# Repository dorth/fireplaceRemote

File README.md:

fireplaceRemote
===============

Arduino project for a remote control to a gas fireplace

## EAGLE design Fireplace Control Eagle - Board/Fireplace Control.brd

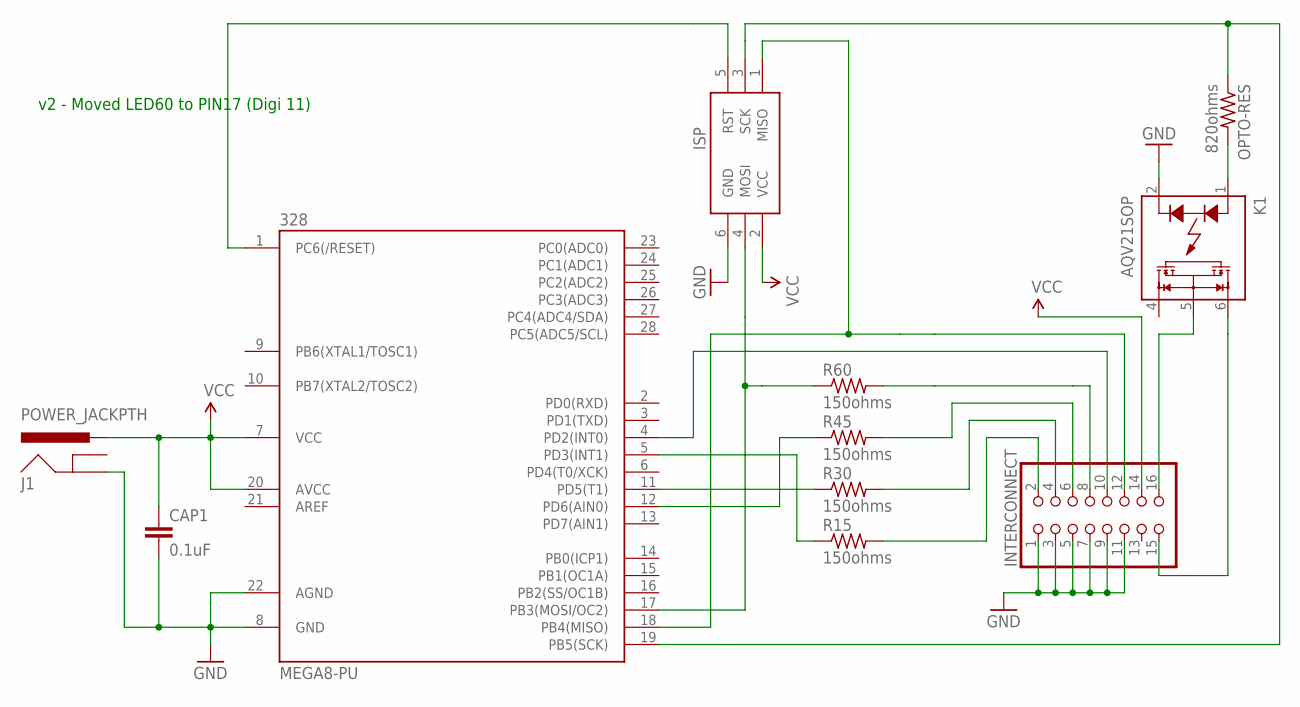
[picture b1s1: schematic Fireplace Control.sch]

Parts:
328: MEGA8-PU; DIL28-3
CAP1: 0.1uF; CAP-PTH-SMALL-KIT
INTERCONNECT: PINHD-2X8; 2X08
ISP: AVRISP-6; AVRISP
J1: POWER_JACKPTH; POWER_JACK_PTH
K1: AQV21SOP; SOP06
OPTO-RES: 820ohms; 0207/2V
R15, R30, R45, R60: 150ohms; 0207/2V

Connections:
15+: INTERCONNECT.2, R15.2
30+: INTERCONNECT.4, R30.2
45+: INTERCONNECT.6, R45.2
60+: INTERCONNECT.8, R60.2
GND: 328.8 (GND), 328.22 (AGND), CAP1.2, INTERCONNECT.1, INTERCONNECT.3, INTERCONNECT.5, INTERCONNECT.7, INTERCONNECT.9, INTERCONNECT.11, ISP.6 (GND), J1.GND, K1.2 (K)
unnamed: 328.11 (PD5(T1)), R30.1
unnamed: INTERCONNECT.15, K1.6 (D1)
unnamed: 328.12 (PD6(AIN0)), R45.1
unnamed: 328.17 (PB3(MOSI/OC2)), ISP.4 (MOSI), R60.1
unnamed: K1.1 (A), OPTO-RES.2
unnamed: 328.19 (PB5(SCK)), ISP.3 (SCK), OPTO-RES.1
unnamed: 328.18 (PB4(MISO)), INTERCONNECT.12, ISP.1 (MISO)
unnamed: INTERCONNECT.16, K1.5 (S)
unnamed: 328.5 (PD3(INT1)), R15.1
unnamed: 328.1 (PC6(/RESET)), ISP.5 (RST)
unnamed: 328.4 (PD2(INT0)), INTERCONNECT.10
VCC: 328.7 (VCC), 328.20 (AVCC), CAP1.1, INTERCONNECT.14, ISP.2 (VCC), J1.PWR

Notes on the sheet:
v2 - Moved LED60 to PIN17 (Digi 11)

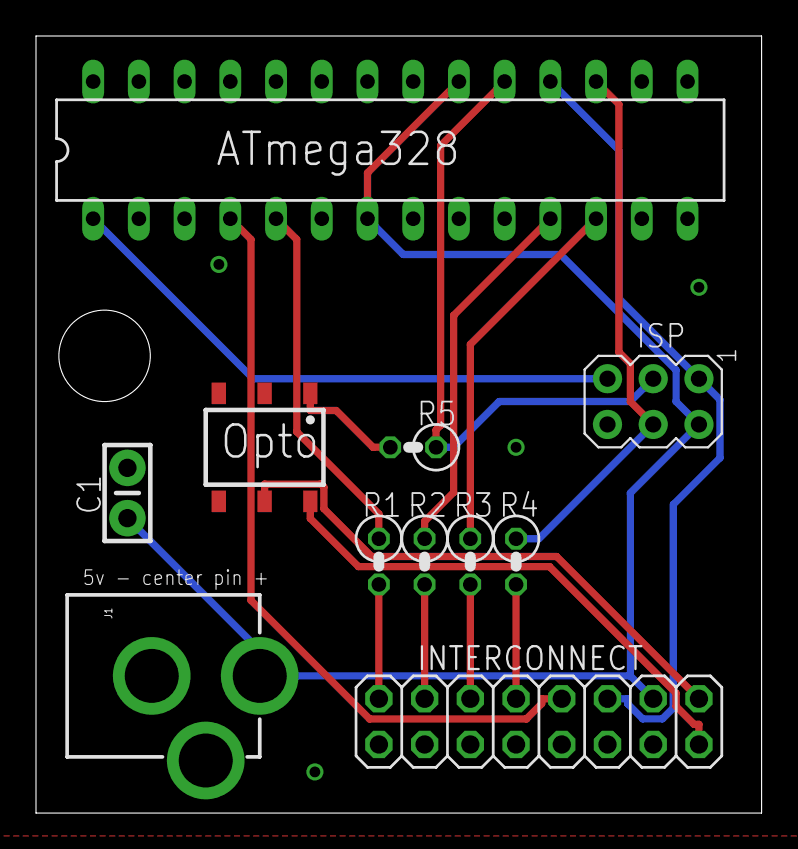
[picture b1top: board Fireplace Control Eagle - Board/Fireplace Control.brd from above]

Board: 2 copper layers, 40.3 x 43.2 mm, 11 parts (0 on the bottom side), 17 nets.

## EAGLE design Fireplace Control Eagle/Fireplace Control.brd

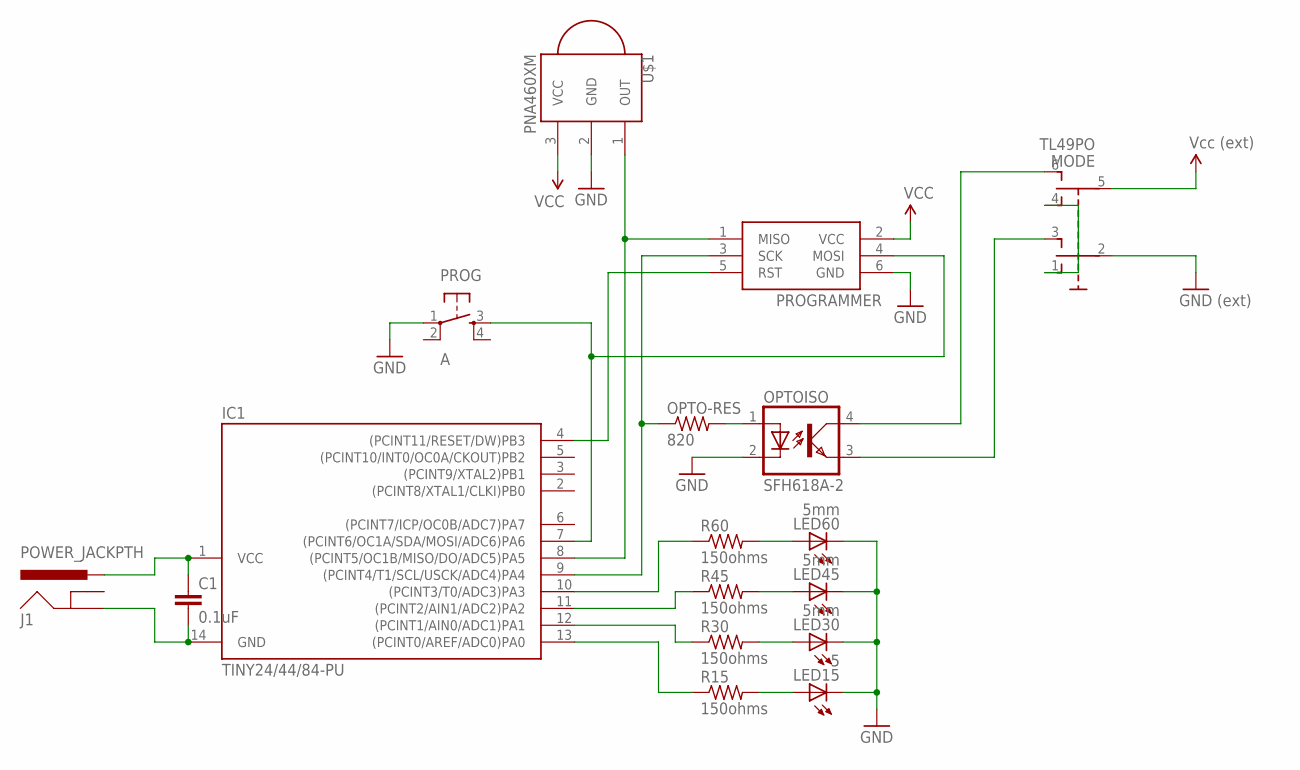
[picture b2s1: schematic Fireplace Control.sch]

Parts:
C1: 0.1uF; CAP-PTH-SMALL-KIT
IC1: TINY24/44/84-PU; DIL14
J1: POWER_JACKPTH; POWER_JACK_PTH
LED15: 5; LED3MM
LED30, LED45, LED60: 5mm; LED3MM
MODE: TL49PO; TL4XPO
OPTO-RES: 820; 0411/15
OPTOISO: SFH618A-2; DIP4
PROG: A; TACTILE-PTH
PROGRAMMER: AVRISP-6; AVRISP
R15, R30, R45, R60: 150ohms; 0411/15
U$1: PNA460XM

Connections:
GND: C1.2, IC1.14 (GND), J1.GND, LED15.K (C), LED30.K (C), LED45.K (C), LED60.K (C), MODE.2, OPTOISO.2 (C), PROG.1, PROGRAMMER.6 (GND), U$1.2 (GND)
unnamed: LED15.A, R15.2
unnamed: LED30.A, R30.2
unnamed: LED45.A, R45.2
unnamed: LED60.A, R60.2
unnamed: IC1.13 ((PCINT0/AREF/ADC0)PA0), R15.1
unnamed: IC1.12 ((PCINT1/AIN0/ADC1)PA1), R30.1
unnamed: IC1.11 ((PCINT2/AIN1/ADC2)PA2), R45.1
unnamed: IC1.10 ((PCINT3/T0/ADC3)PA3), R60.1
unnamed: OPTO-RES.2, OPTOISO.1 (A)
unnamed: IC1.7 ((PCINT6/OC1A/SDA/MOSI/ADC6)PA6), PROG.3, PROGRAMMER.4 (MOSI)
unnamed: IC1.9 ((PCINT4/T1/SCL/USCK/ADC4)PA4), OPTO-RES.1, PROGRAMMER.3 (SCK)
unnamed: IC1.8 ((PCINT5/OC1B/MISO/DO/ADC5)PA5), PROGRAMMER.1 (MISO), U$1.1 (OUT)
unnamed: MODE.1 (O), MODE.4 (O1)
unnamed: MODE.6 (S1), OPTOISO.4 (COL)
unnamed: MODE.3 (S), OPTOISO.3 (EMIT)
unnamed: IC1.4 ((PCINT11/RESET/DW)PB3), PROGRAMMER.5 (RST)
VCC: C1.1, IC1.1 (VCC), J1.PWR, MODE.5 (P1), PROGRAMMER.2 (VCC), U$1.3 (VCC)

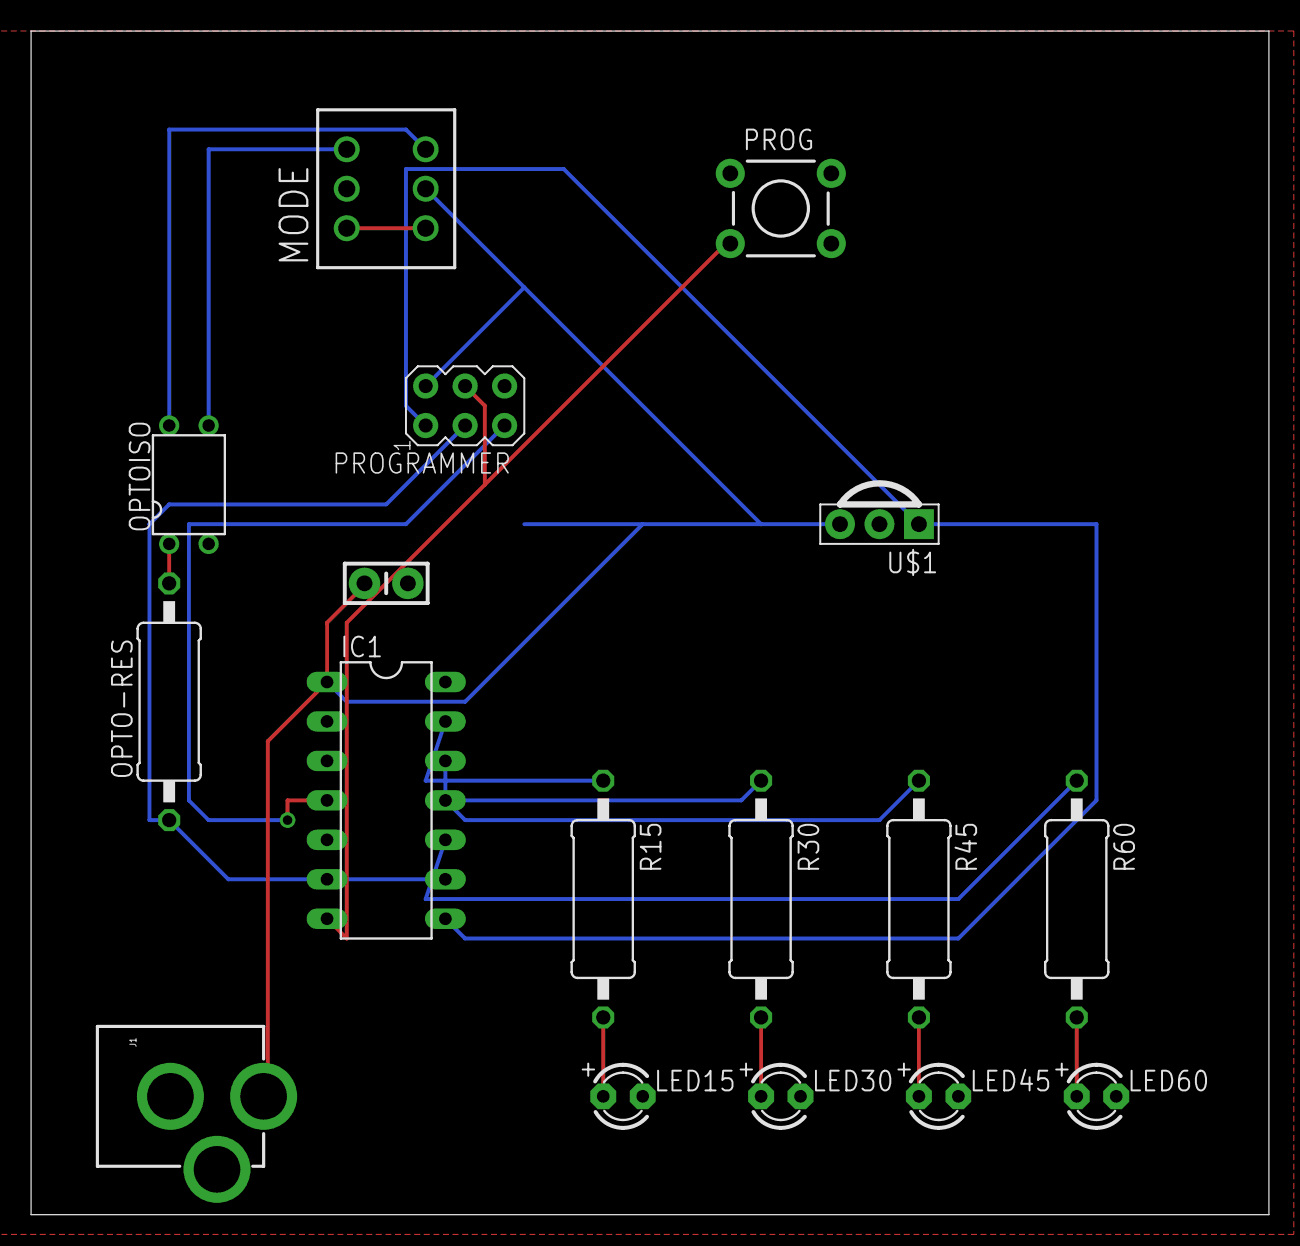
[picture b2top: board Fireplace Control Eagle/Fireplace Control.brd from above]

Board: 2 copper layers, 79.7 x 76.2 mm, 17 parts (0 on the bottom side), 18 nets.

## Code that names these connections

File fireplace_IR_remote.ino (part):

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
// LED Indicators for 0 min, 15 min, 30 min, 45 min, and 60 minutes
const int led00         = 99;          // Bogus or unused
const int led15         = 0; 	       // PA0, Physical Pin #13  Should be a PWM capable pin for warningLight
const int led30         = 1; 	       // PA1, Physical Pin #12
const int led45         = 2; 	       // PA2, Physical Pin #11
const int led60         = 3; 	       // PA3, Physical Pin #10

const int fireplacePin  = 4;           // PA4, Physical Pin #9 - pin to activate optoisolator to turn on fireplace
const int irReceivePin  = 5;           // PA5, Physical Pin #8 - pin connected to IR detector output
const int pushButton    = 6;           // PA6, Physical Pin #7 - hooked to MOM-PB. Enable PullUP resistor!  
                                       // the value on the pin goes LOW when the button is pressed
#else

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
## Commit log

2013-02-14 Initial Fritzing document. Will probably need to move this all to Eagle
2013-02-14 2009/02/09 Version of this sketch
2013-02-14 2013/02/13 Version of sketch
2013-02-14 2013-02-14 - Test Commit with new editor
2013-02-14 Added Eagle Layout Files
2013-02-14 Removing Time.h library - now keeping track of time on my own
    Time.h and TimerAlarm.h consumed 2,320 bytes of program space. Since I
    was only depending on them to track "simple minutes", I removed them and
    will now keep track of time by using millis
2013-02-14 Adjusting WARNING period LED visual
    Yanking some duplicate logic out of the main loop and creating a
    SHUTDOWN_WARNING_PERIOD boolean to keep track of things. Clarified the
    names of some constants. Restored the outside "if" statement of "if
    (fireplaceOn)" into the countDownTimer loop as I believe it was correct
    in the first place and not causing the weird issues I ran into before.
2013-02-15 Updated logic for stop/start
    Starting worked fine. Stopping via the timer worked fine. However,
    stopping from a button press was NOT working because there was no logic
    to stop the fireplace outside the countDownTimer routine. This adds
    shutdown logic in the main loop should fireplaceMinutes go to 0.
2013-02-22 Control Panel Layout
    Measured drawing of layout for control panel
2013-02-22 Board Layout initial Checkin
    Since many components will not exist on the PCB, I created a new layout
    with a 16 pin header which will "jump" to the external devices. I'll
    bet Eagle can do this, but I wasn't sure.
2013-02-23 Submitted to OSHPark
    This is the design that went to OSHPark for productions
2013-03-04 Fixed shutdown logic on buttonpress
    Moved the shutdown into a function since it needed to happen both for a
    timer expire as well as for a button press "off".
2013-03-04 Not really sure what these are used for
    Not really sure when these showed up or what they are for. FIgured I'd
    sync them up though just in case.
2013-03-17 FreeRoute Additions
    Files used for FreeRoute (DSN, dru and SCRs)
2013-03-18 First cut v2 Board
    Rewired led60 to use pin 11 (instead of 9). Re-routed using FreeRoute

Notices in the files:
parts and their libraries:
SparkFun-Connectors: Licensing: CC v3.0 Share-Alike You are welcome to use this library for commercial purposes.
